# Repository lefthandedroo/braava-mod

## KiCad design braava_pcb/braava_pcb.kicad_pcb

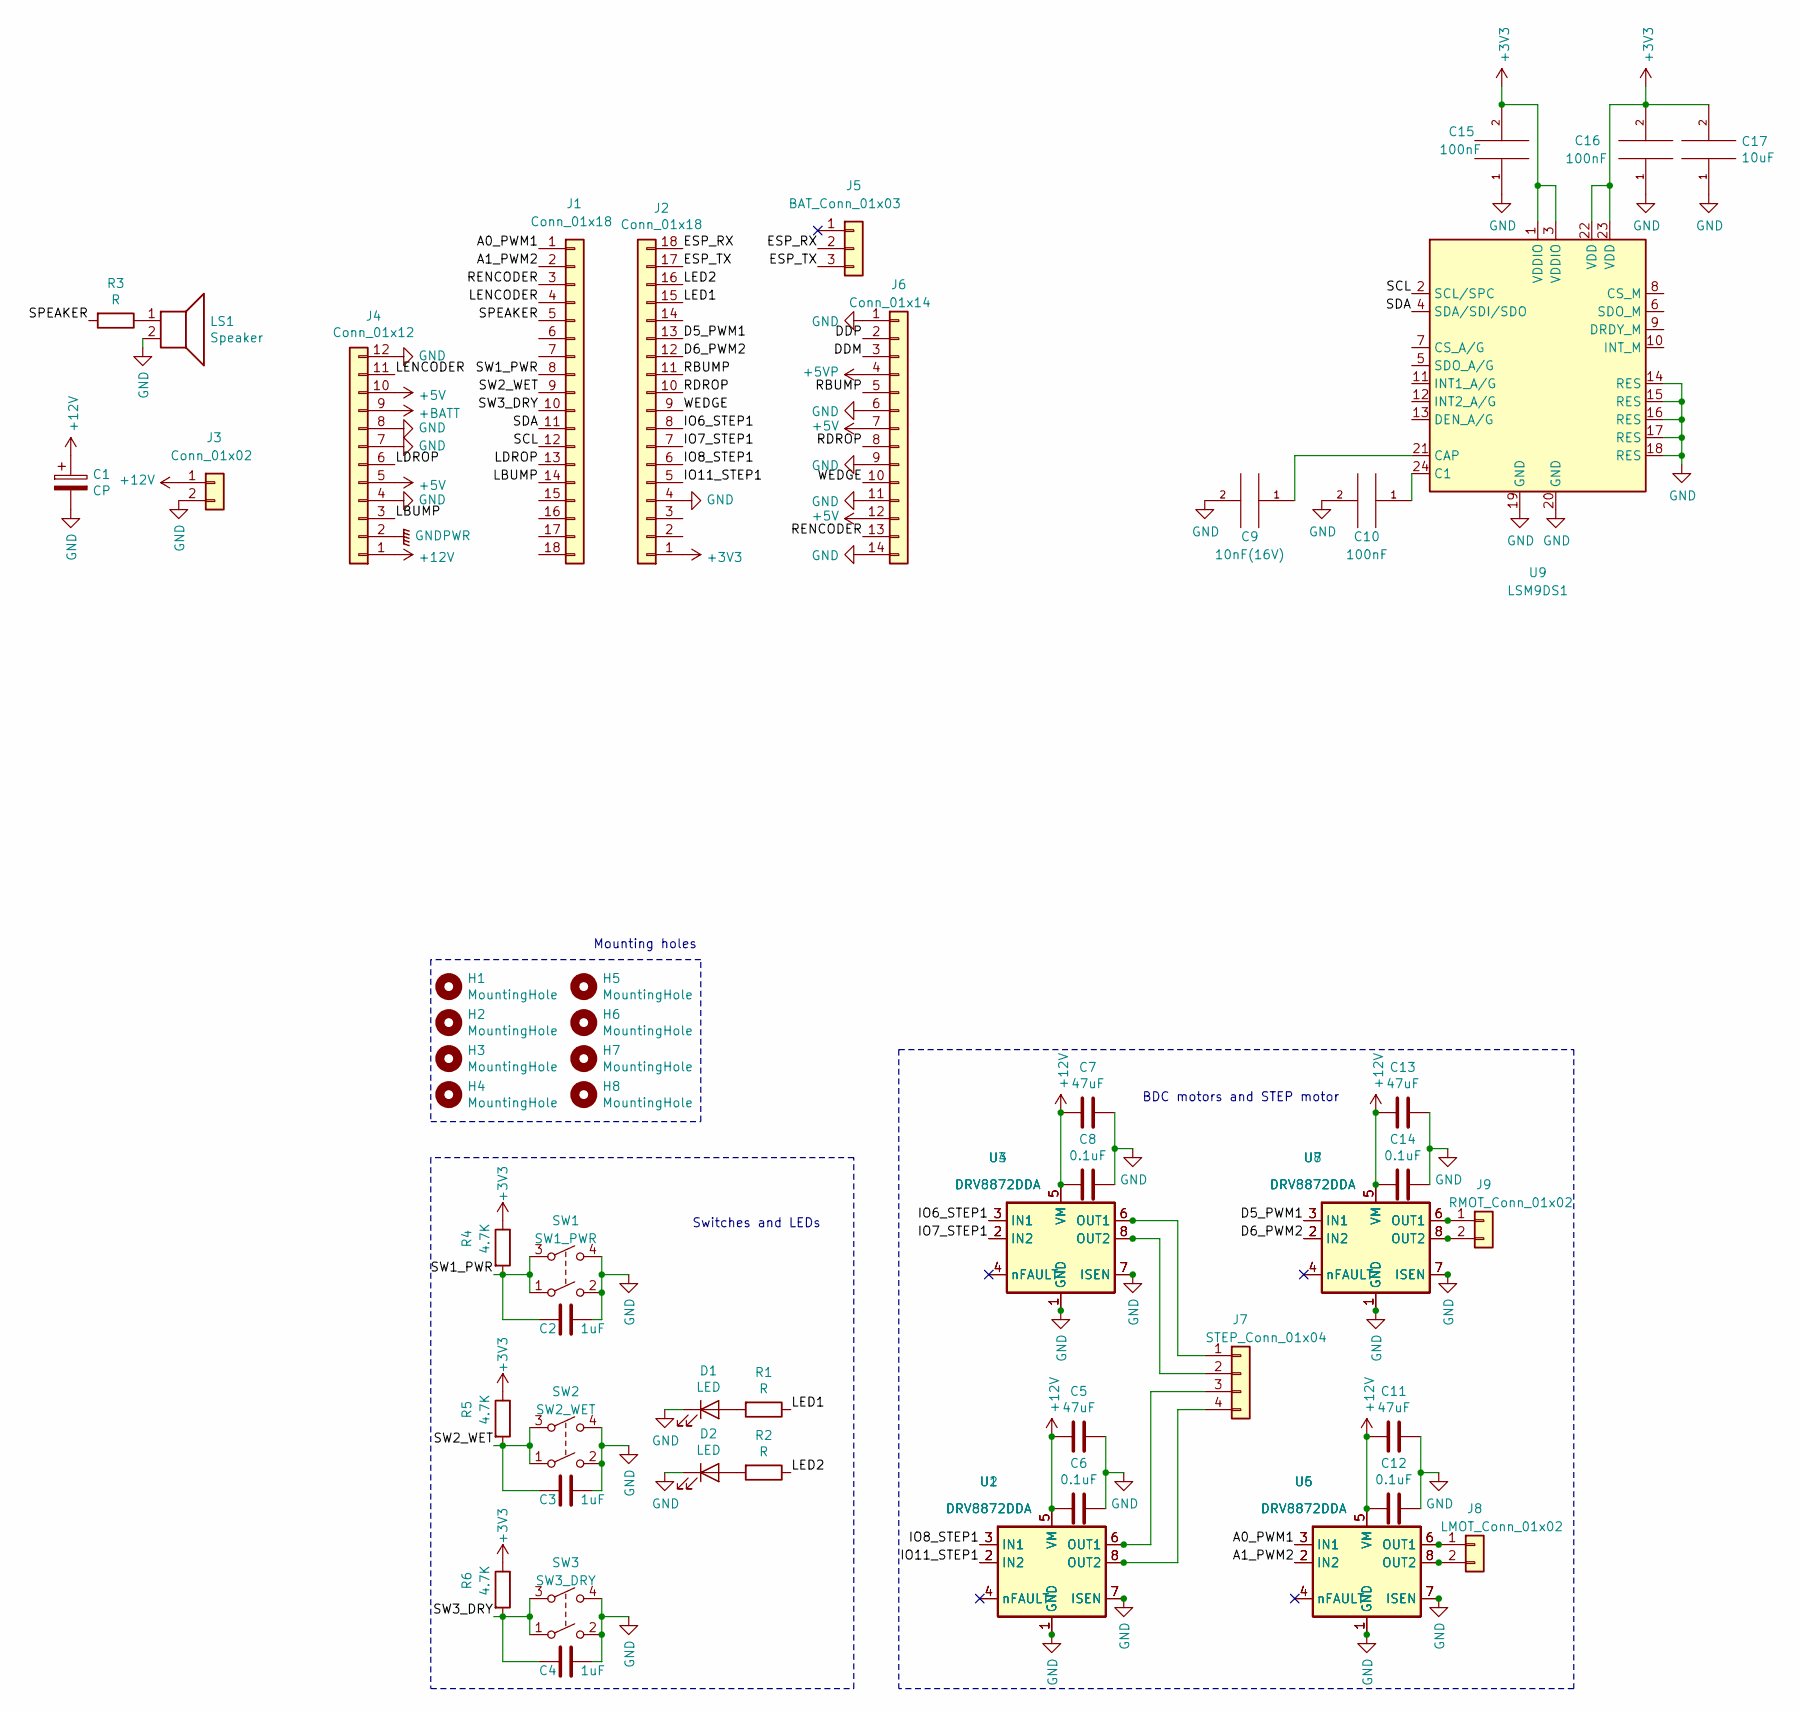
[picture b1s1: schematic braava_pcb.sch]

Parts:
C1: CP; CP_Radial_D8.0mm_P3.50mm
C2, C3, C4: 1uF; C_0603_1608Metric
C5, C7, C11, C13: 47uF; C_0603_1608Metric
C6, C8, C12, C14: 0.1uF; C_0603_1608Metric
C9: 10nF(16V); C_0603_1608Metric
C10, C15, C16: 100nF; C_0603_1608Metric
C17: 10uF; C_0603_1608Metric
D1, D2: LED; LED_0603_1608Metric
H1, H2, H3, H4, H5, H6: MountingHole; MountingHole_2.5mm
H7, H8: MountingHole; MountingHole_2.1mm
J1, J2: Conn_01x18; PinHeader_1x18_P2.54mm_Vertical
J3: Conn_01x02; JST_PH_B2B-PH-K_1x02_P2.00mm_Vertical
J4: Conn_01x12; JST_PH_B12B-PH-K_1x12_P2.00mm_Vertical
J5: BAT_Conn_01x03; JST_PH_B3B-PH-K_1x03_P2.00mm_Vertical
J6: Conn_01x14; JST_PH_B14B-PH-K_1x14_P2.00mm_Vertical
J7: STEP_Conn_01x04; PinHeader_1x04_P2.54mm_Vertical
J8: LMOT_Conn_01x02; JST_PH_B2B-PH-K_1x02_P2.00mm_Vertical
J9: RMOT_Conn_01x02; JST_PH_B2B-PH-K_1x02_P2.00mm_Vertical
LS1: Speaker; Buzzer_15x7.5RM7.6
R1, R2, R3: R; R_0603_1608Metric
R4, R5, R6: 4.7K; R_0603_1608Metric
SW1: SW1_PWR
SW2: SW2_WET
SW3: SW3_DRY
U1, U2, U3, U4, U5, U6, U7, U8: DRV8872DDA; Texas_HTSOP-8-1EP_3.9x4.9mm_P1.27mm_EP2.95x4.9mm_Mask2.4x3.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
U9: LSM9DS1; LGA-24L_3x3.5mm_P0.43mm

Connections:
+3V3: C15.2, C16.2, C17.2, J2.1, R4.1, R5.1, R6.1, U9.1 (VDDIO), U9.3 (VDDIO), U9.22 (VDD), U9.23 (VDD)
+5V: J4.5, J4.10, J6.7, J6.12
+5VP: J6.4
+12V: C1.1, C5.2, C6.2, C7.2, C8.2, C11.2, C12.2, C13.2, C14.2, J3.1, J4.1, U1.5 (VM), U2.5 (VM), U3.5 (VM), U4.5 (VM), U5.5 (VM), U6.5 (VM), U7.5 (VM), U8.5 (VM)
+BATT: J4.9
/A0_PWM1: J1.1, U5.3 (IN1), U6.3 (IN1)
/A1_PWM2: J1.2, U5.2 (IN2), U6.2 (IN2)
/D5_PWM1: J2.13, U7.3 (IN1), U8.3 (IN1)
/D6_PWM2: J2.12, U7.2 (IN2), U8.2 (IN2)
/DDM: J6.3
/DDP: J6.2
/ESP_RX: J2.18, J5.2
/ESP_TX: J2.17, J5.3
/IO6_STEP1: J2.8, U3.3 (IN1), U4.3 (IN1)
/IO7_STEP1: J2.7, U3.2 (IN2), U4.2 (IN2)
/IO8_STEP1: J2.6, U1.3 (IN1), U2.3 (IN1)
/IO11_STEP1: J2.5, U1.2 (IN2), U2.2 (IN2)
/LBUMP: J1.14, J4.3
/LDROP: J1.13, J4.6
/LED1: J2.15, R1.1
/LED2: J2.16, R2.1
/LENCODER: J1.4, J4.11
/RBUMP: J2.11, J6.5
/RDROP: J2.10, J6.8
/RENCODER: J1.3, J6.13
/SCL: J1.12, U9.2 (SCL/SPC)
/SDA: J1.11, U9.4 (SDA/SDI/SDO)
/SPEAKER: J1.5, R3.2
/SW1_PWR: C2.2, J1.8, R4.2, SW1.1, SW1.3
/SW2_WET: C3.2, J1.9, R5.2, SW2.1, SW2.3
/SW3_DRY: C4.2, J1.10, R6.2, SW3.1, SW3.3
/WEDGE: J2.9, J6.10
GND: C1.2, C2.1, C3.1, C4.1, C5.1, C6.1, C7.1, C8.1, C9.2, C10.2, C11.1, C12.1, C13.1, C14.1, C15.1, C16.1, C17.1, D1.1 (K), D2.1 (K), J2.4, J3.2, J4.4, J4.7, J4.8, J4.12, J6.1, J6.6, J6.9, J6.11, J6.14, LS1.2, SW1.2, SW1.4, SW2.2, SW2.4, SW3.2, SW3.4, U1.1 (GND), U1.7 (ISEN), U1.9 (GND), U2.1 (GND), U2.7 (ISEN), U2.9 (GND), U3.1 (GND), U3.7 (ISEN), U3.9 (GND), U4.1 (GND), U4.7 (ISEN), U4.9 (GND), U5.1 (GND), U5.7 (ISEN), U5.9 (GND), U6.1 (GND), U6.7 (ISEN), U6.9 (GND), U7.1 (GND), U7.7 (ISEN), U7.9 (GND), U8.1 (GND), U8.7 (ISEN), U8.9 (GND), U9.14 (RES), U9.15 (RES), U9.16 (RES), U9.17 (RES), U9.18 (RES), U9.19 (GND), U9.20 (GND)
GNDPWR: J4.2
unnamed: C9.1, U9.21 (CAP)
unnamed: C10.1, U9.24 (C1)
unnamed: D1.2 (A), R1.2
unnamed: D2.2 (A), R2.2
unnamed: J7.1, U3.6 (OUT1), U4.6 (OUT1)
unnamed: J7.2, U3.8 (OUT2), U4.8 (OUT2)
unnamed: J7.3, U1.6 (OUT1), U2.6 (OUT1)
unnamed: J7.4, U1.8 (OUT2), U2.8 (OUT2)
unnamed: J8.1, U5.6 (OUT1), U6.6 (OUT1)
unnamed: J8.2, U5.8 (OUT2), U6.8 (OUT2)
unnamed: J9.1, U7.6 (OUT1), U8.6 (OUT1)
unnamed: J9.2, U7.8 (OUT2), U8.8 (OUT2)
unnamed: LS1.1, R3.1
unnamed: U1.4 (nFAULT), U2.4 (nFAULT)
unnamed: U3.4 (nFAULT), U4.4 (nFAULT)
unnamed: U5.4 (nFAULT), U6.4 (nFAULT)
unnamed: U7.4 (nFAULT), U8.4 (nFAULT)

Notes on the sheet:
Switches and LEDs
BDC motors and STEP motor
Mounting holes

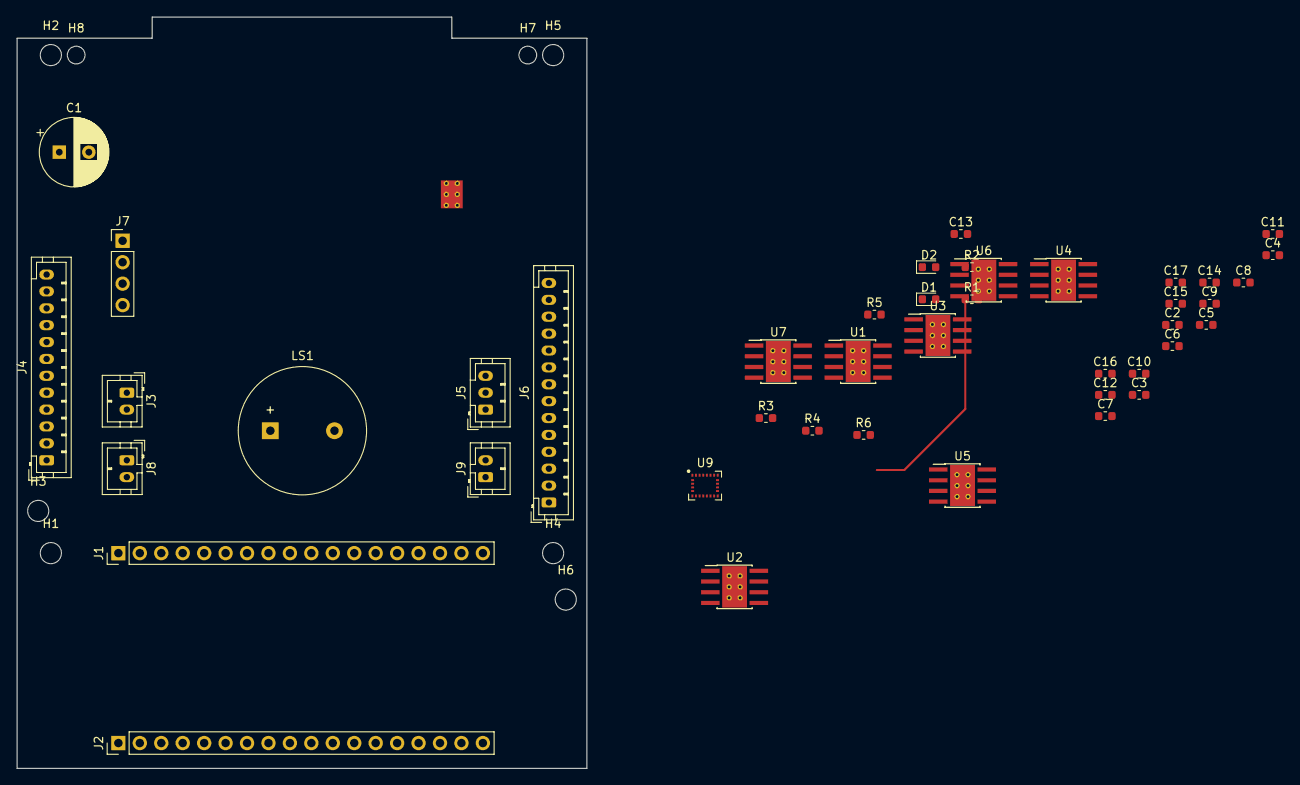
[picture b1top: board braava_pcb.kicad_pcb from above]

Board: 4 copper layers, 67.5 x 89.0 mm, 52 parts (1 on the bottom side), 46 nets.

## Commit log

2020-03-22 pcb start
2020-03-22 Most components added to schematic
2020-03-29 Motors, switches near completed
2020-05-05 Added touch switches library. Started component placement.
